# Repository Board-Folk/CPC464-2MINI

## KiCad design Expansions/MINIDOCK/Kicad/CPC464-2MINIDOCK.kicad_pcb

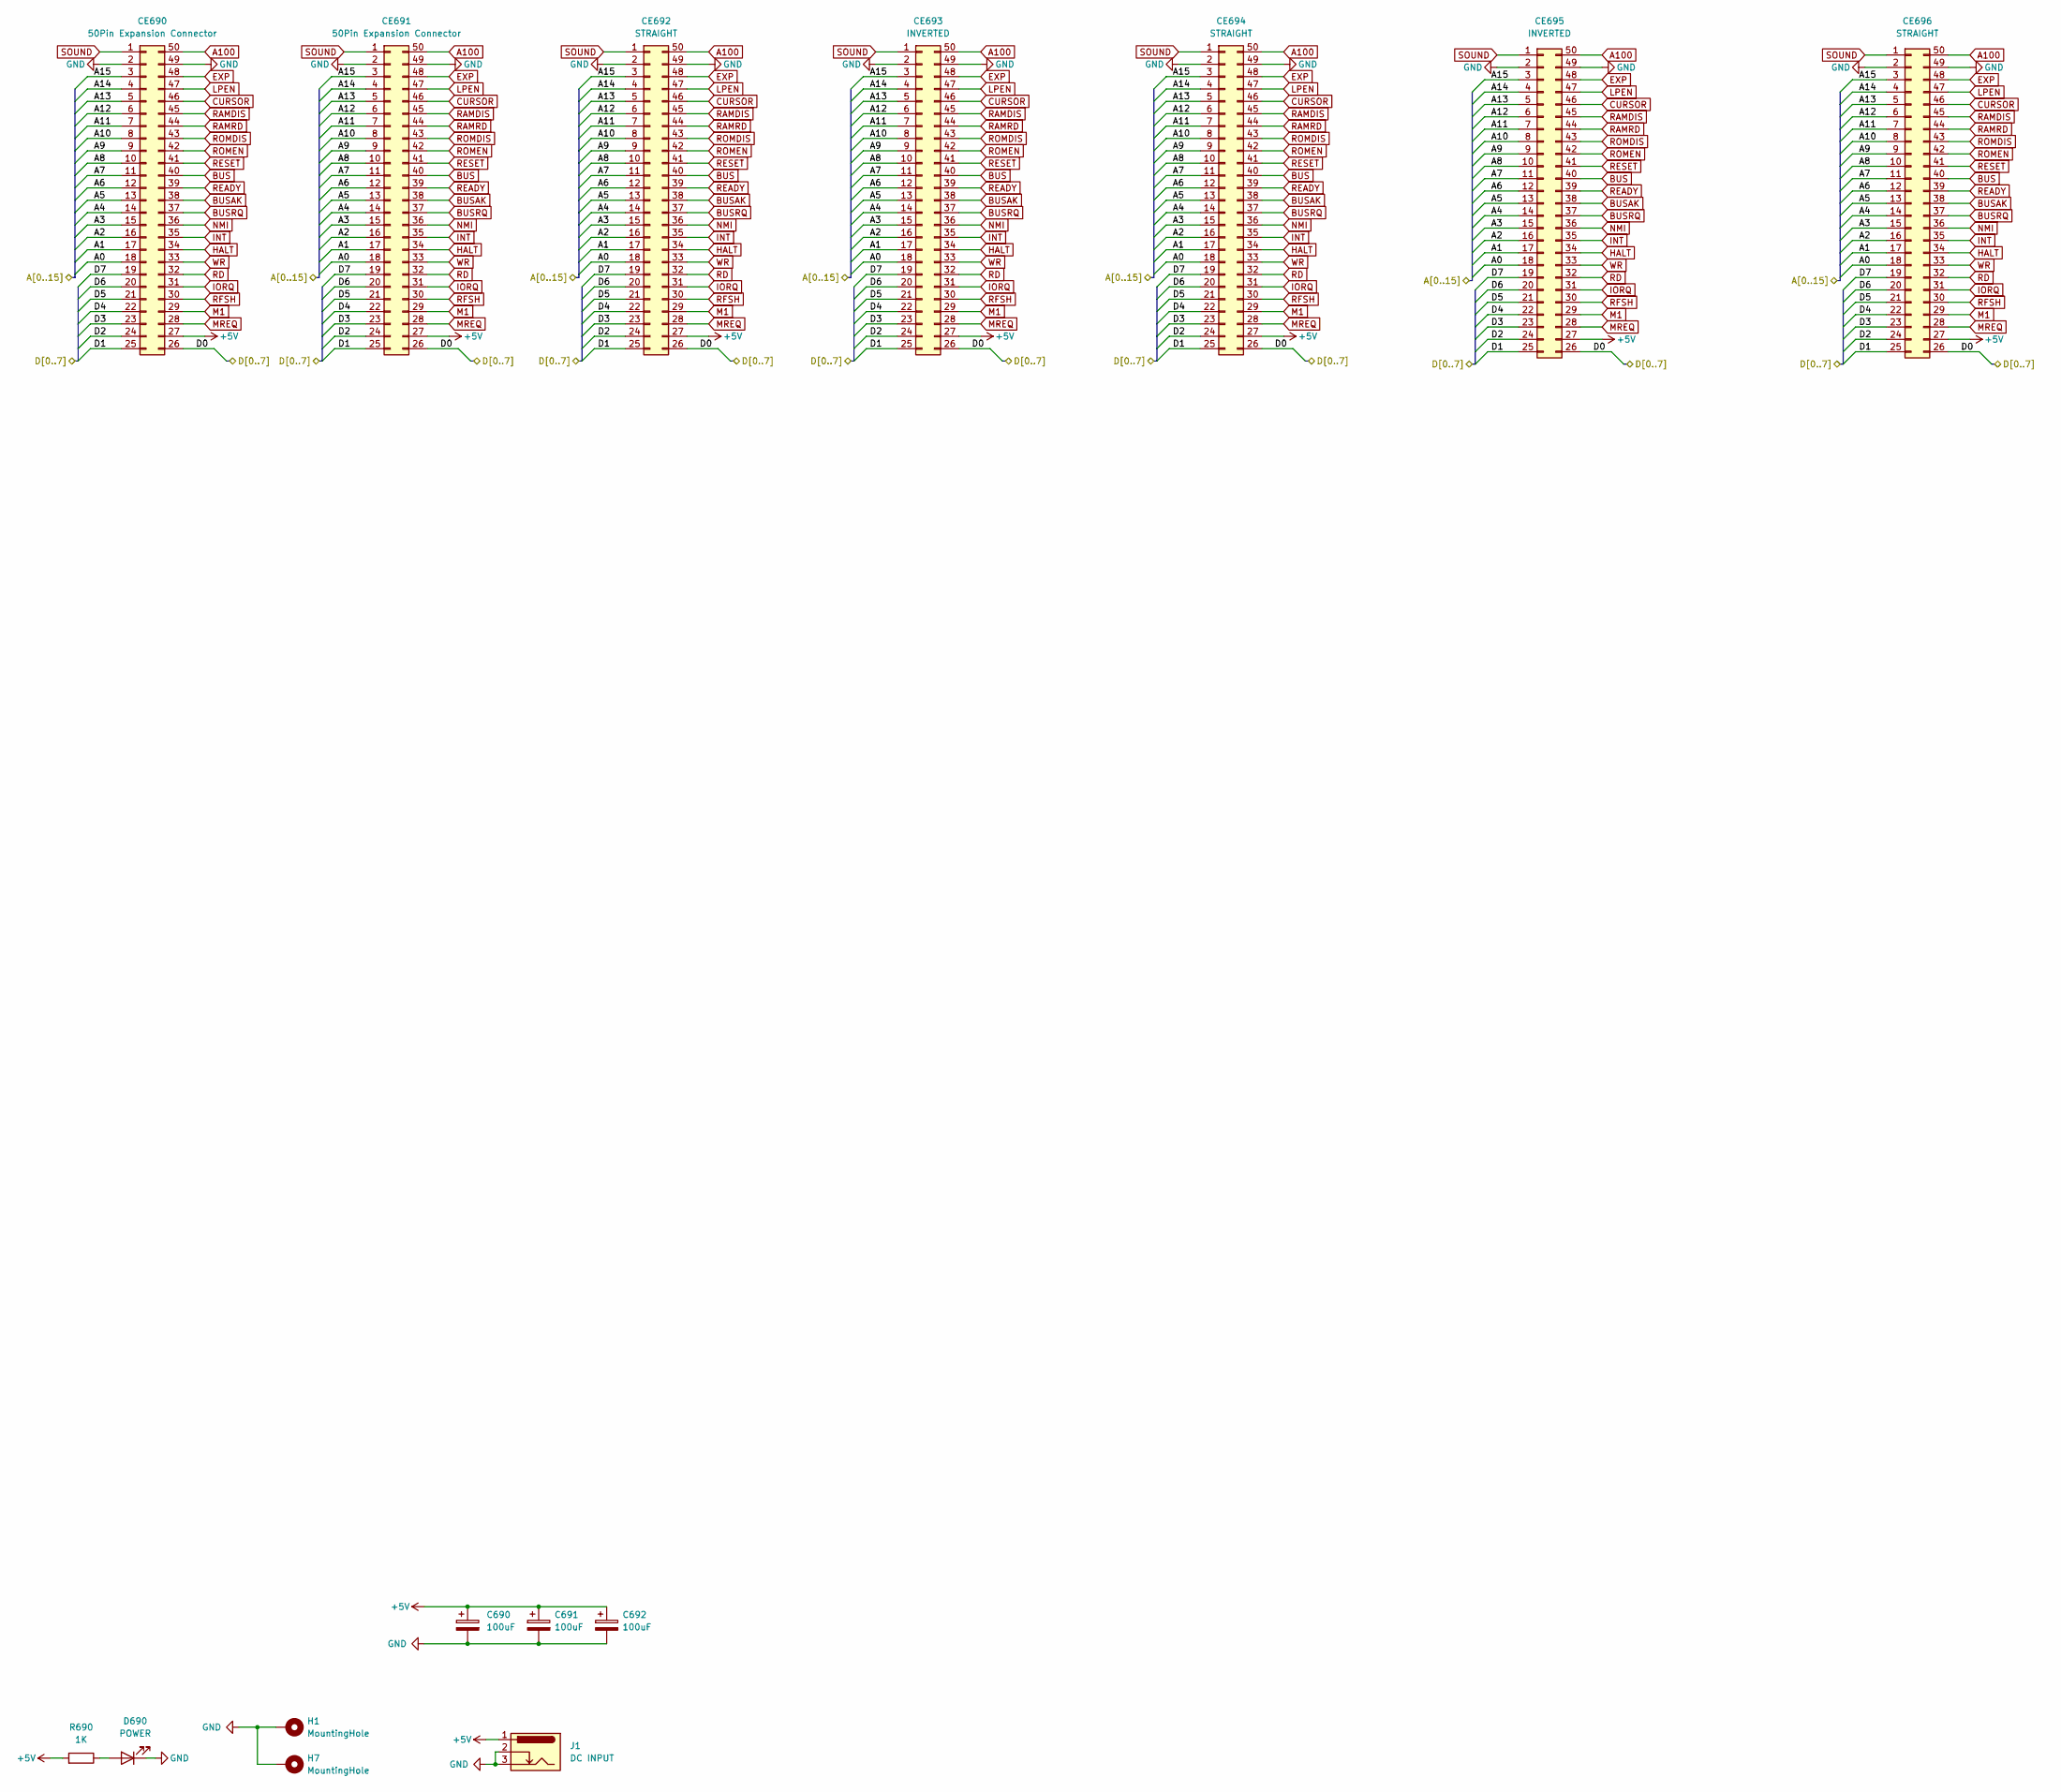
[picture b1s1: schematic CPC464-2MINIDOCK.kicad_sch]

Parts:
C690, C691, C692: 100uF; CP_Radial_D6.3mm_P2.50mm
CE690, CE691: 50Pin Expansion Connector; EXPANSION_IDC_ANONYMISED
CE692, CE694, CE696: STRAIGHT; EXPANSION_IDC_EXP_STRAIGHT
CE693, CE695: INVERTED; EXPANSION_IDC_EXP_INVERTED
D690: POWER; LED_1206_3216Metric
H1, H7: MountingHole; MountingHole_2.7mm_M2.5_ISO14580_Pad
J1: DC INPUT; BarrelJack_Horizontal
R690: 1K; R_0805_2012Metric

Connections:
+5V: C690.1, C691.1, C692.1, CE690.27, CE691.27, CE692.27, CE693.27, CE694.27, CE695.27, CE696.27, J1.1, R690.2
/A0: CE690.18, CE691.18, CE692.18, CE693.18, CE694.18, CE695.18, CE696.18
/A1: CE690.17, CE691.17, CE692.17, CE693.17, CE694.17, CE695.17, CE696.17
/A2: CE690.16, CE691.16, CE692.16, CE693.16, CE694.16, CE695.16, CE696.16
/A3: CE690.15, CE691.15, CE692.15, CE693.15, CE694.15, CE695.15, CE696.15
/A4: CE690.14, CE691.14, CE692.14, CE693.14, CE694.14, CE695.14, CE696.14
/A5: CE690.13, CE691.13, CE692.13, CE693.13, CE694.13, CE695.13, CE696.13
/A6: CE690.12, CE691.12, CE692.12, CE693.12, CE694.12, CE695.12, CE696.12
/A7: CE690.11, CE691.11, CE692.11, CE693.11, CE694.11, CE695.11, CE696.11
/A8: CE690.10, CE691.10, CE692.10, CE693.10, CE694.10, CE695.10, CE696.10
/A9: CE690.9, CE691.9, CE692.9, CE693.9, CE694.9, CE695.9, CE696.9
/A10: CE690.8, CE691.8, CE692.8, CE693.8, CE694.8, CE695.8, CE696.8
/A11: CE690.7, CE691.7, CE692.7, CE693.7, CE694.7, CE695.7, CE696.7
/A12: CE690.6, CE691.6, CE692.6, CE693.6, CE694.6, CE695.6, CE696.6
/A13: CE690.5, CE691.5, CE692.5, CE693.5, CE694.5, CE695.5, CE696.5
/A14: CE690.4, CE691.4, CE692.4, CE693.4, CE694.4, CE695.4, CE696.4
/A15: CE690.3, CE691.3, CE692.3, CE693.3, CE694.3, CE695.3, CE696.3
/D0: CE690.26, CE691.26, CE692.26, CE693.26, CE694.26, CE695.26, CE696.26
/D1: CE690.25, CE691.25, CE692.25, CE693.25, CE694.25, CE695.25, CE696.25
/D2: CE690.24, CE691.24, CE692.24, CE693.24, CE694.24, CE695.24, CE696.24
/D3: CE690.23, CE691.23, CE692.23, CE693.23, CE694.23, CE695.23, CE696.23
/D4: CE690.22, CE691.22, CE692.22, CE693.22, CE694.22, CE695.22, CE696.22
/D5: CE690.21, CE691.21, CE692.21, CE693.21, CE694.21, CE695.21, CE696.21
/D6: CE690.20, CE691.20, CE692.20, CE693.20, CE694.20, CE695.20, CE696.20
/D7: CE690.19, CE691.19, CE692.19, CE693.19, CE694.19, CE695.19, CE696.19
A100: CE690.50, CE691.50, CE692.50, CE693.50, CE694.50, CE695.50, CE696.50
BUS: CE690.40, CE691.40, CE692.40, CE693.40, CE694.40, CE695.40, CE696.40
BUSAK: CE690.38, CE691.38, CE692.38, CE693.38, CE694.38, CE695.38, CE696.38
BUSRQ: CE690.37, CE691.37, CE692.37, CE693.37, CE694.37, CE695.37, CE696.37
CURSOR: CE690.46, CE691.46, CE692.46, CE693.46, CE694.46, CE695.46, CE696.46
EXP: CE690.48, CE691.48, CE692.48, CE693.48, CE694.48, CE695.48, CE696.48
GND: C690.2, C691.2, C692.2, CE690.2, CE690.49, CE691.2, CE691.49, CE692.2, CE692.49, CE693.2, CE693.49, CE694.2, CE694.49, CE695.2, CE695.49, CE696.2, CE696.49, D690.1 (K), H1.1, H7.1, J1.2, J1.3
HALT: CE690.34, CE691.34, CE692.34, CE693.34, CE694.34, CE695.34, CE696.34
INT: CE690.35, CE691.35, CE692.35, CE693.35, CE694.35, CE695.35, CE696.35
IORQ: CE690.31, CE691.31, CE692.31, CE693.31, CE694.31, CE695.31, CE696.31
LPEN: CE690.47, CE691.47, CE692.47, CE693.47, CE694.47, CE695.47, CE696.47
M1: CE690.29, CE691.29, CE692.29, CE693.29, CE694.29, CE695.29, CE696.29
MREQ: CE690.28, CE691.28, CE692.28, CE693.28, CE694.28, CE695.28, CE696.28
NMI: CE690.36, CE691.36, CE692.36, CE693.36, CE694.36, CE695.36, CE696.36
unnamed: D690.2 (A), R690.1
RAMDIS: CE690.45, CE691.45, CE692.45, CE693.45, CE694.45, CE695.45, CE696.45
RAMRD: CE690.44, CE691.44, CE692.44, CE693.44, CE694.44, CE695.44, CE696.44
RD: CE690.32, CE691.32, CE692.32, CE693.32, CE694.32, CE695.32, CE696.32
READY: CE690.39, CE691.39, CE692.39, CE693.39, CE694.39, CE695.39, CE696.39
RESET: CE690.41, CE691.41, CE692.41, CE693.41, CE694.41, CE695.41, CE696.41
RFSH: CE690.30, CE691.30, CE692.30, CE693.30, CE694.30, CE695.30, CE696.30
ROMDIS: CE690.43, CE691.43, CE692.43, CE693.43, CE694.43, CE695.43, CE696.43
ROMEN: CE690.42, CE691.42, CE692.42, CE693.42, CE694.42, CE695.42, CE696.42
SOUND: CE690.1, CE691.1, CE692.1, CE693.1, CE694.1, CE695.1, CE696.1
WR: CE690.33, CE691.33, CE692.33, CE693.33, CE694.33, CE695.33, CE696.33

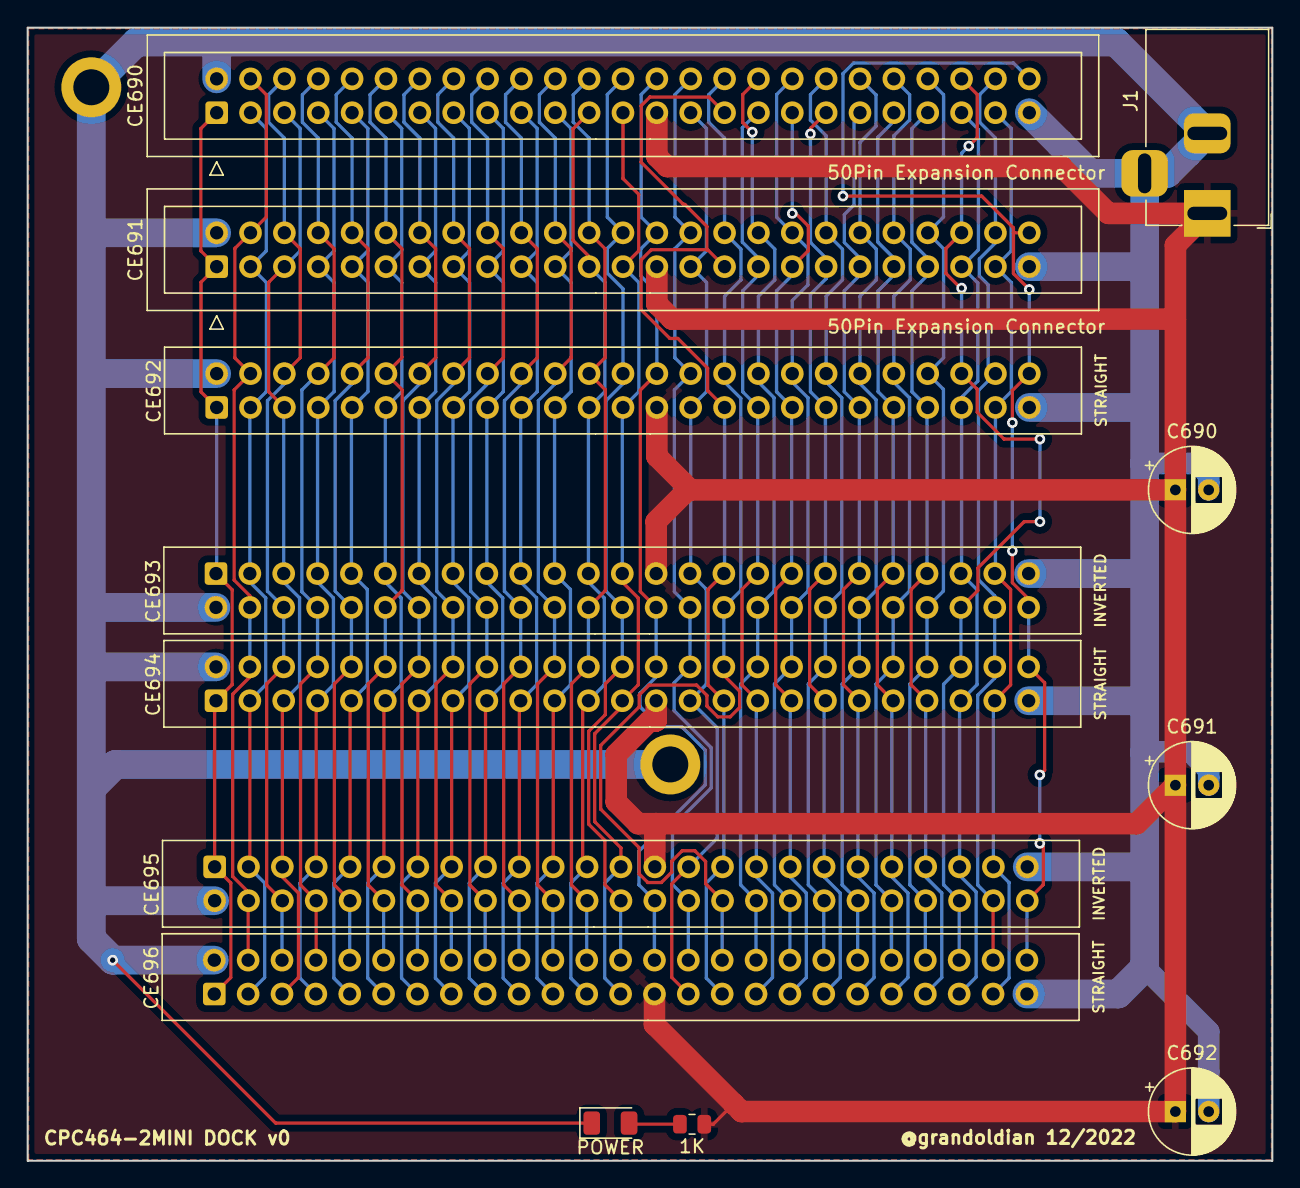
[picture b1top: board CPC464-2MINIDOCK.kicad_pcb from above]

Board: 2 copper layers, 93.4 x 85.0 mm, 15 parts (0 on the bottom side), 50 nets.
